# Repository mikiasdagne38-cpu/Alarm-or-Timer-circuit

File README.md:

# Alarm-or-Timer-circuit
It is an Alarm or Timer circuit using a standalone microcontroller chip instead of a pre-made Arduino board. I use the 4 buttons to set a time. The ATmega328P chip counts down the seconds using its crystal clock and shows the remaining time on the 4-digit display. When time runs out, the chip turns on the LED and sounds the buzzer.

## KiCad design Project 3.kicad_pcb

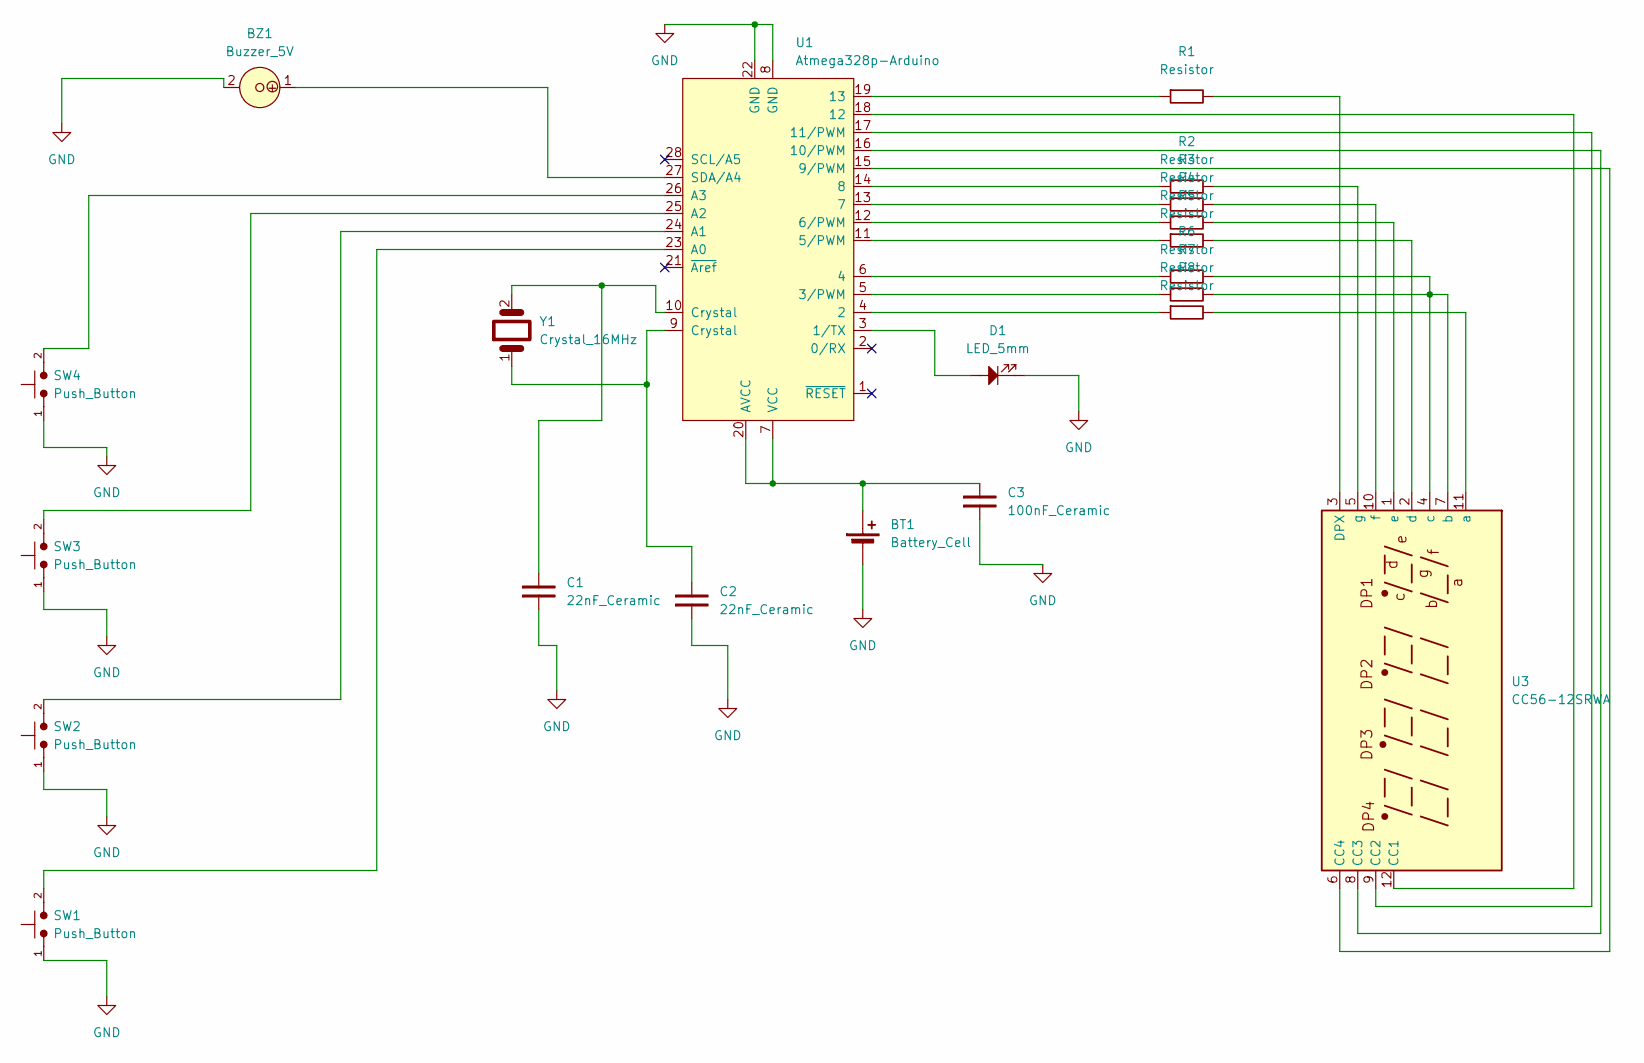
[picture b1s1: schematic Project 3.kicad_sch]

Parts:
BT1: Battery_Cell; TerminalBlock_Xinya_XY308-2.54-2P_1x02_P2.54mm_Horizontal
BZ1: Buzzer_5V; MagneticBuzzer_ProSignal_ABT-410-RC
C1, C2: 22nF_Ceramic; C_Disc_D3.0mm_W2.0mm_P2.50mm
C3: 100nF_Ceramic; C_Disc_D3.0mm_W2.0mm_P2.50mm
D1: LED_5mm; LED_D5.0mm
R1, R2, R3, R4, R5, R6, R7, R8: Resistor; R_Axial_DIN0207_L6.3mm_D2.5mm_P10.16mm_Horizontal
SW1, SW2, SW3, SW4: Push_Button; SW_PUSH_6mm
U1: Atmega328p-Arduino; DIP-28_W7.62mm_LongPads
U3: CC56-12SRWA; CA56-12SRWA
Y1: Crystal_16MHz; Crystal_HC49-4H_Vertical

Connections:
GND: BT1.2 (-), BZ1.2, C1.1, C2.1, C3.1, D1.1, SW1.1, SW2.1, SW3.1, SW4.1, U1.8 (GND), U1.22 (GND)
unnamed: BT1.1 (+), C3.2, U1.7 (VCC), U1.20 (AVCC)
unnamed: C1.2, U1.10 (Crystal), Y1.2
unnamed: C2.2, U1.9 (Crystal), Y1.1
unnamed: D1.2, U1.3 (1/TX)
unnamed: R8.1, U1.4 (2)
unnamed: R7.1, U1.5 (3/PWM)
unnamed: R6.1, U1.6 (4)
unnamed: R5.1, U1.11 (5/PWM)
unnamed: R4.1, U1.12 (6/PWM)
unnamed: R3.1, U1.13 (7)
unnamed: R2.1, U1.14 (8)
unnamed: U1.15 (9/PWM), U3.6 (CC4)
unnamed: U1.16 (10/PWM), U3.8 (CC3)
unnamed: U1.17 (11/PWM), U3.9 (CC2)
unnamed: U1.18 (12), U3.12 (CC1)
unnamed: R1.1, U1.19 (13)
unnamed: SW1.2, U1.23 (A0)
unnamed: SW2.2, U1.24 (A1)
unnamed: SW3.2, U1.25 (A2)
unnamed: SW4.2, U1.26 (A3)
unnamed: BZ1.1, U1.27 (SDA/A4)
unnamed: R1.2, U3.3 (DPX)
unnamed: R8.2, U3.11 (a)
unnamed: R6.2, R7.2, U3.4 (c), U3.7 (b)
unnamed: R5.2, U3.2 (d)
unnamed: R4.2, U3.1 (e)
unnamed: R3.2, U3.10 (f)
unnamed: R2.2, U3.5 (g)

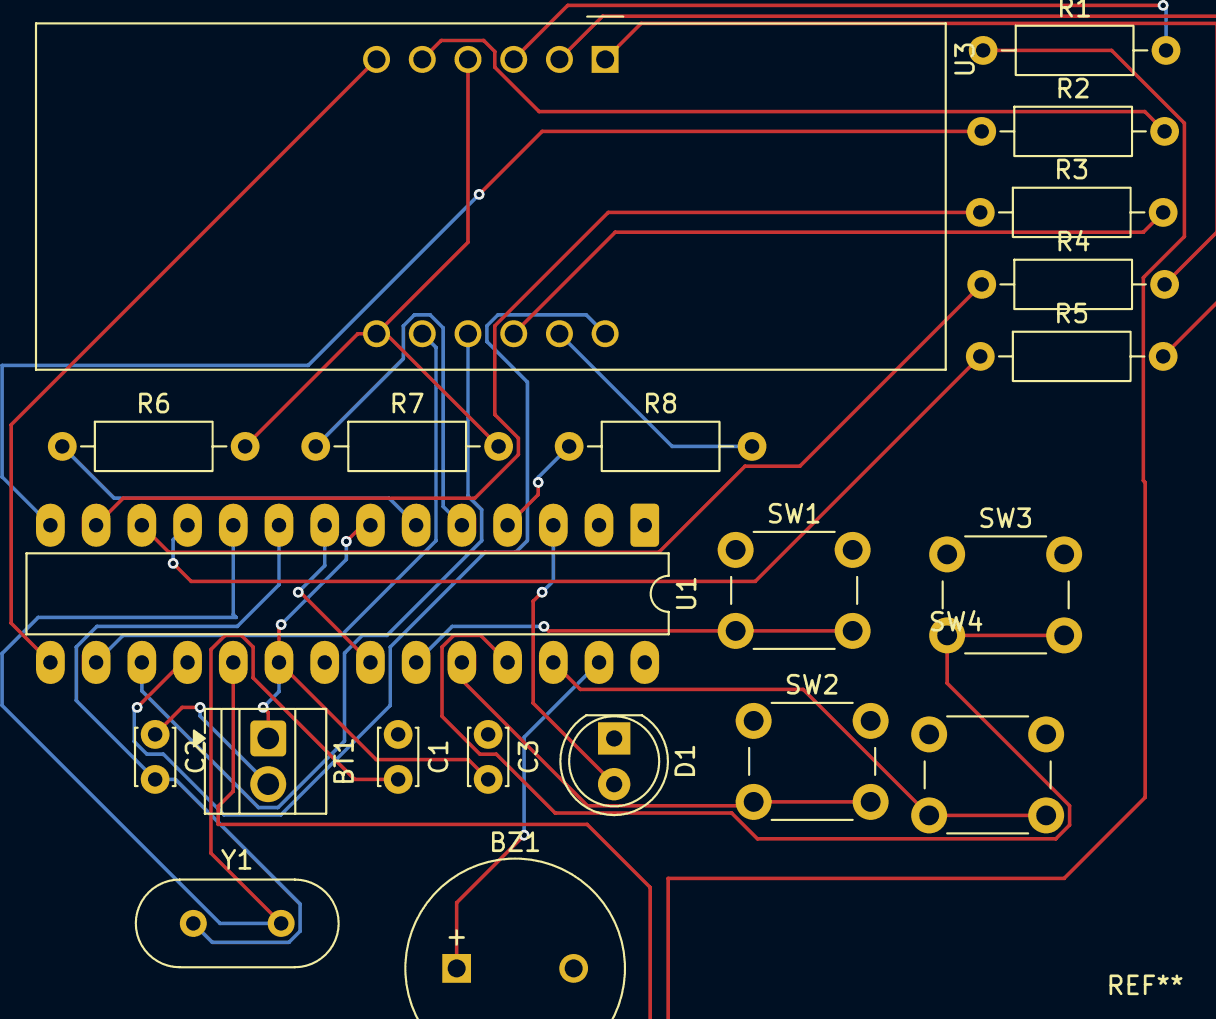
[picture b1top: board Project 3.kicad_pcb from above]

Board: 2 copper layers, 21 parts (0 on the bottom side), 29 nets.
